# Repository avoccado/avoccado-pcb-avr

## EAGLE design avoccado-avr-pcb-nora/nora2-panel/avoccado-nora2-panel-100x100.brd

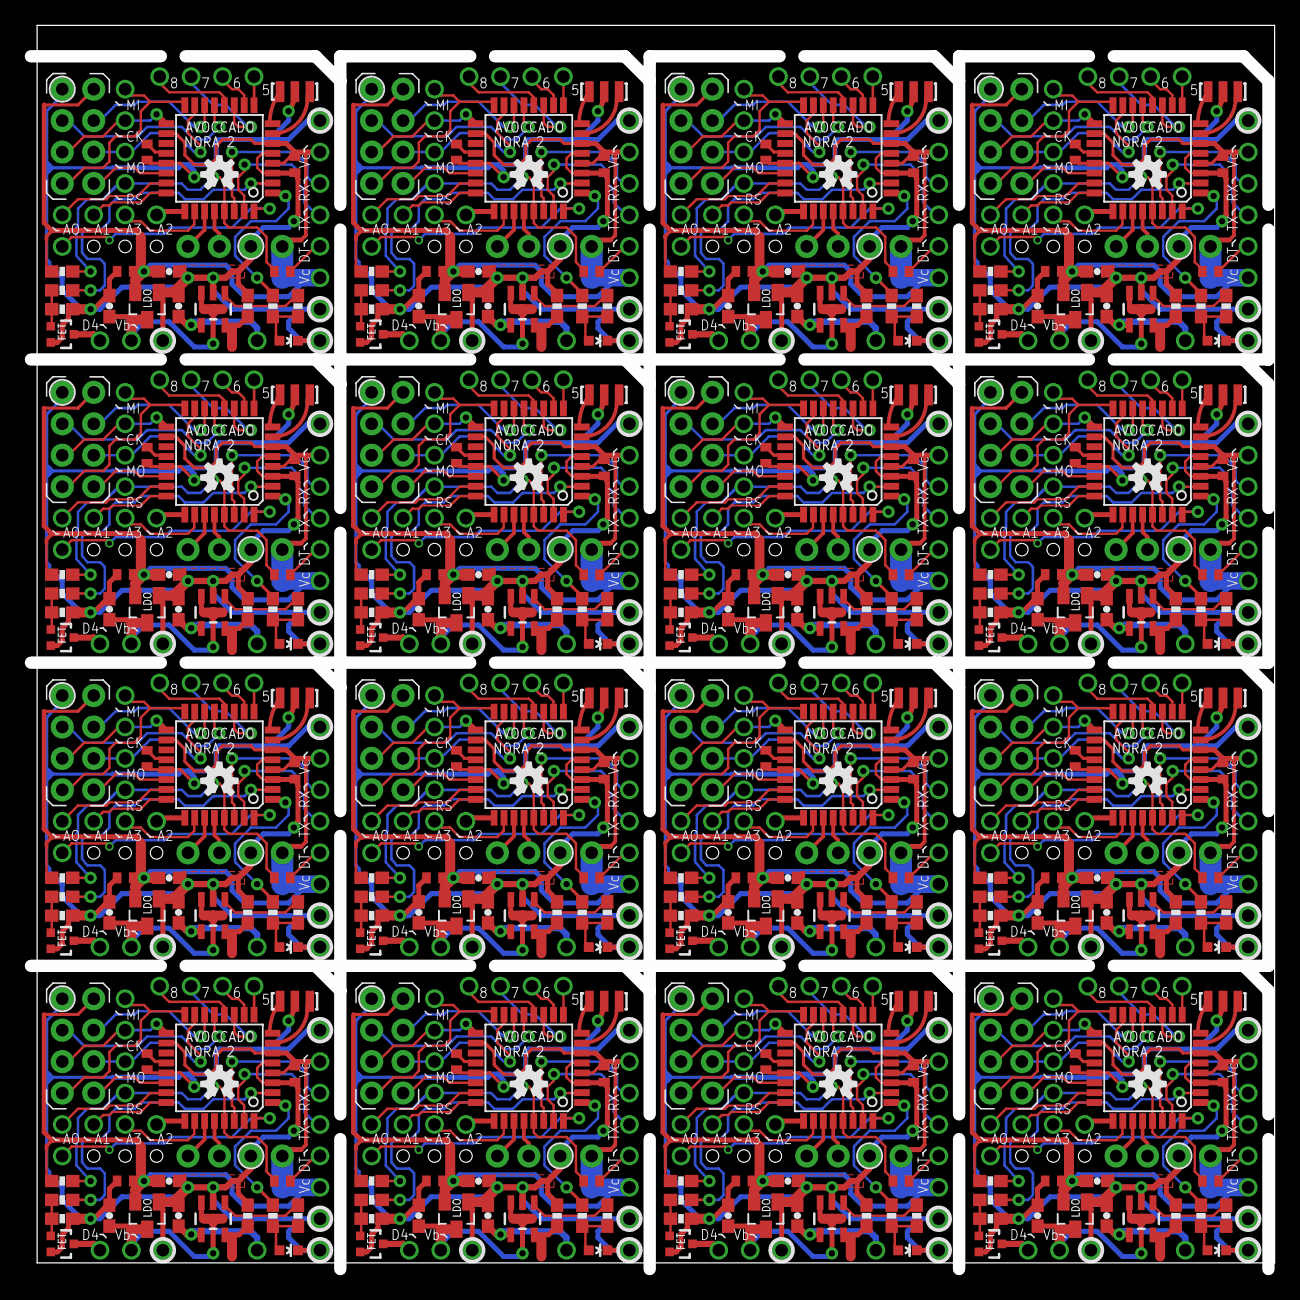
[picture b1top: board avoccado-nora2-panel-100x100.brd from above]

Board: 2 copper layers, 100.0 x 100.0 mm, 816 parts (0 on the bottom side), 560 nets.

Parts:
AVR, AVR1, AVR2, AVR3, AVR4, AVR5, AVR6, AVR7, AVR8, AVR9, AVR10, AVR11, AVR12, AVR13, AVR14, AVR15: ATMEGA328P; TQFP32-08
C1, C2, C3, C7, C8, C9, C10, C12, C15, C16, C17, C19, C22, C23, C24, C26, C29, C30, C31, C33, C36, C37, C38, C40, C43, C44, C45, C47, C50, C51, C52, C54, C57, C58, C59, C61, C64, C65, C66, C68, C71, C72, C73, C75, C78, C79, C80, C82, C85, C86, C87, C89, C92, C93, C94, C96, C99, C100, C101, C103, C106, C107, C108, C110: 0.1uF; C0402
C4, C5, C6, C11, C13, C14, C18, C20, C21, C25, C27, C28, C32, C34, C35, C39, C41, C42, C46, C48, C49, C53, C55, C56, C60, C62, C63, C67, C69, C70, C74, C76, C77, C81, C83, C84, C88, C90, C91, C95, C97, C98, C102, C104, C105, C109, C111, C112: 4.7uF; 0603-CAP
D1, D2, D3, D4, D5, D6, D7, D8, D9, D10, D11, D12, D13, D14, D15, D16: LED; LED-0603
JP1, JP3, JP6, JP7, JP8, JP9, JP10, JP11, JP12, JP13, JP14, JP15, JP16, JP17, JP18, JP19, JP20, JP21, JP22, JP23, JP24, JP25, JP26, JP30, JP31, JP32, JP33, JP34, JP35, JP36, JP37, JP38, JP39, JP40, JP41, JP42, JP43, JP44, JP45, JP46, JP53, JP54, JP55, JP56, JP57, JP58, JP59, JP60, JP61, JP62, JP63, JP64, JP65, JP66, JP67, JP68, JP69, JP70, JP71, JP72, JP79, JP80, JP81, JP82, JP83, JP84, JP85, JP86, JP87, JP88, JP89, JP90, JP91, JP92, JP93, JP94, JP95, JP96, JP97, JP98, JP105, JP106, JP107, JP108, JP109, JP110, JP111, JP112, JP113, JP114, JP115, JP116, JP117, JP118, JP119, JP120, JP121, JP122, JP123, JP124, JP131, JP132, JP133, JP134, JP135, JP136, JP137, JP138, JP139, JP140, JP141, JP142, JP143, JP144, JP145, JP146, JP147, JP148, JP149, JP150, JP157, JP158, JP159, JP160, JP161, JP162, JP163, JP164, JP165, JP166, JP167, JP168, JP169, JP170, JP171, JP172, JP173, JP174, JP175, JP176, JP183, JP184, JP185, JP186, JP187, JP188, JP189, JP190, JP191, JP192, JP193, JP194, JP195, JP196, JP197, JP198, JP199, JP200, JP201, JP202, JP209, JP210, JP211, JP212, JP213, JP214, JP215, JP216, JP217, JP218, JP219, JP220, JP221, JP222, JP223, JP224, JP225, JP226, JP227, JP228, JP235, JP236, JP237, JP238, JP239, JP240, JP241, JP242, JP243, JP244, JP245, JP246, JP247, JP248, JP249, JP250, JP251, JP252, JP253, JP254, JP261, JP262, JP263, JP264, JP265, JP266, JP267, JP268, JP269, JP270, JP271, JP272, JP273, JP274, JP275, JP276, JP277, JP278, JP279, JP280, JP287, JP288, JP289, JP290, JP291, JP292, JP293, JP294, JP295, JP296, JP297, JP298, JP299, JP300, JP301, JP302, JP303, JP304, JP305, JP306, JP313, JP314, JP315, JP316, JP317, JP318, JP319, JP320, JP321, JP322, JP323, JP324, JP325, JP326, JP327, JP328, JP329, JP330, JP331, JP332, JP339, JP340, JP341, JP342, JP343, JP344, JP345, JP346, JP347, JP348, JP349, JP350, JP351, JP352, JP353, JP354, JP355, JP356, JP357, JP358, JP365, JP366, JP367, JP368, JP369, JP370, JP371, JP372, JP373, JP374, JP375, JP376, JP377, JP378, JP379, JP380, JP381, JP382, JP383, JP384, JP391, JP392, JP393, JP394, JP395, JP396, JP397, JP398, JP399, JP400, JP401, JP402, JP403, JP404, JP405, JP406, JP407, JP408, JP409, JP410: M01NOSILK-KIT; 1X01NS-KIT
JP2, JP4, JP5, JP27, JP28, JP29, JP47, JP48, JP49, JP50, JP51, JP52, JP73, JP74, JP75, JP76, JP77, JP78, JP99, JP100, JP101, JP102, JP103, JP104, JP125, JP126, JP127, JP128, JP129, JP130, JP151, JP152, JP153, JP154, JP155, JP156, JP177, JP178, JP179, JP180, JP181, JP182, JP203, JP204, JP205, JP206, JP207, JP208, JP229, JP230, JP231, JP232, JP233, JP234, JP255, JP256, JP257, JP258, JP259, JP260, JP281, JP282, JP283, JP284, JP285, JP286, JP307, JP308, JP309, JP310, JP311, JP312, JP333, JP334, JP335, JP336, JP337, JP338, JP359, JP360, JP361, JP362, JP363, JP364, JP385, JP386, JP387, JP388, JP389, JP390, JP411, JP412, JP413, JP414, JP415, JP416: M021X02_NO_SILK; 1X02_NO_SILK
LDO, LDO1, LDO2, LDO3, LDO4, LDO5, LDO6, LDO7, LDO8, LDO9, LDO10, LDO11, LDO12, LDO13, LDO14, LDO15: MCP1703CB; SOT23
LOGO1, LOGO2, LOGO3, LOGO4, LOGO5, LOGO6, LOGO7, LOGO8, LOGO9, LOGO10, LOGO11, LOGO12, LOGO13, LOGO14, LOGO15, LOGO16: OSHW-LOGOS; OSHW-LOGO-S
Q1, Q3, Q5, Q7, Q9, Q11, Q13, Q15, Q17, Q19, Q21, Q23, Q25, Q27, Q29, Q31: 16MHz; RESONATOR-SMD
Q2, Q4, Q6, Q8, Q10, Q12, Q14, Q16, Q18, Q20, Q22, Q24, Q26, Q28, Q30, Q32: FET; SOT323
R1, R4, R6, R8, R10, R12, R14, R16, R18, R20, R22, R24, R26, R28, R30, R32, R34, R36, R38, R40, R42, R44, R46, R48, R50, R52, R54, R56, R58, R60, R62, R64, R66, R68, R70, R72, R74, R76, R78, R80, R82, R84, R86, R88, R90, R92, R94, R96: 1K; 0603-RES
R2, R7, R13, R19, R25, R31, R37, R43, R49, R55, R61, R67, R73, R79, R85, R91: 10K; 0603-RES
R3, R9, R15, R21, R27, R33, R39, R45, R51, R57, R63, R69, R75, R81, R87, R93: Rp; 0603-RES
R5, R11, R17, R23, R29, R35, R41, R47, R53, R59, R65, R71, R77, R83, R89, R95: 1M; 0603-RES
TP1, TP2, TP3, TP4, TP5, TP6, TP7, TP8, TP9, TP10, TP11, TP12, TP13, TP14, TP15, TP16, TP17, TP18, TP19, TP20, TP21, TP22, TP23, TP24, TP25, TP26, TP27, TP28, TP29, TP30, TP31, TP32, TP33, TP34, TP35, TP36, TP37, TP38, TP39, TP40, TP41, TP42, TP43, TP44, TP45, TP46, TP47, TP48, TP49, TP50, TP51, TP52, TP53, TP54, TP55, TP56, TP57, TP58, TP59, TP60, TP61, TP62, TP63, TP64, TP65, TP66, TP67, TP68, TP69, TP70, TP71, TP72, TP73, TP74, TP75, TP76, TP77, TP78, TP79, TP80: M01NOSILK-KIT; 1X01NS-KIT
U1, U2, U3, U4, U5, U6, U7, U8, U9, U10, U11, U12, U13, U14, U15, U16: MCP73831; SOT23-5

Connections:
3.3V: AVR.4, AVR.6, AVR.18, C3.2, C6.1, C10.1, JP2.2, JP4.1, JP11.1, JP18.1, LDO.2, R2.2
3.3V1: AVR1.4, AVR1.6, AVR1.18, C7.1, C8.2, C14.1, JP31.1, JP38.1, JP47.2, JP51.1, LDO1.2, R7.2
3.3V2: AVR2.4, AVR2.6, AVR2.18, C15.1, C16.2, C21.1, JP57.1, JP64.1, JP73.2, JP77.1, LDO2.2, R13.2
3.3V3: AVR3.4, AVR3.6, AVR3.18, C22.1, C23.2, C28.1, JP83.1, JP90.1, JP99.2, JP103.1, LDO3.2, R19.2
3.3V4: AVR4.4, AVR4.6, AVR4.18, C29.1, C30.2, C35.1, JP109.1, JP116.1, JP125.2, JP129.1, LDO4.2, R25.2
3.3V5: AVR5.4, AVR5.6, AVR5.18, C36.1, C37.2, C42.1, JP135.1, JP142.1, JP151.2, JP155.1, LDO5.2, R31.2
3.3V6: AVR6.4, AVR6.6, AVR6.18, C43.1, C44.2, C49.1, JP161.1, JP168.1, JP177.2, JP181.1, LDO6.2, R37.2
3.3V7: AVR7.4, AVR7.6, AVR7.18, C50.1, C51.2, C56.1, JP187.1, JP194.1, JP203.2, JP207.1, LDO7.2, R43.2
3.3V8: AVR8.4, AVR8.6, AVR8.18, C57.1, C58.2, C63.1, JP213.1, JP220.1, JP229.2, JP233.1, LDO8.2, R49.2
3.3V9: AVR9.4, AVR9.6, AVR9.18, C64.1, C65.2, C70.1, JP239.1, JP246.1, JP255.2, JP259.1, LDO9.2, R55.2
3.3V10: AVR10.4, AVR10.6, AVR10.18, C71.1, C72.2, C77.1, JP265.1, JP272.1, JP281.2, JP285.1, LDO10.2, R61.2
3.3V11: AVR11.4, AVR11.6, AVR11.18, C78.1, C79.2, C84.1, JP291.1, JP298.1, JP307.2, JP311.1, LDO11.2, R67.2
3.3V12: AVR12.4, AVR12.6, AVR12.18, C85.1, C86.2, C91.1, JP317.1, JP324.1, JP333.2, JP337.1, LDO12.2, R73.2
3.3V13: AVR13.4, AVR13.6, AVR13.18, C92.1, C93.2, C98.1, JP343.1, JP350.1, JP359.2, JP363.1, LDO13.2, R79.2
3.3V14: AVR14.4, AVR14.6, AVR14.18, C99.1, C100.2, C105.1, JP369.1, JP376.1, JP385.2, JP389.1, LDO14.2, R85.2
3.3V15: AVR15.4, AVR15.6, AVR15.18, C106.1, C107.2, C112.1, JP395.1, JP402.1, JP411.2, JP415.1, LDO15.2, R91.2
5V: C4.1, JP17.1, U2.4
5V1: C11.1, JP37.1, U1.4
5V2: C18.1, JP63.1, U3.4
5V3: C25.1, JP89.1, U4.4
5V4: C32.1, JP115.1, U5.4
5V5: C39.1, JP141.1, U6.4
5V6: C46.1, JP167.1, U7.4
5V7: C53.1, JP193.1, U8.4
5V8: C60.1, JP219.1, U9.4
5V9: C67.1, JP245.1, U10.4
5V10: C74.1, JP271.1, U11.4
5V11: C81.1, JP297.1, U12.4
5V12: C88.1, JP323.1, U13.4
5V13: C95.1, JP349.1, U14.4
5V14: C102.1, JP375.1, U15.4
5V15: C109.1, JP401.1, U16.4
A0: AVR.23, JP19.1
A1: AVR.24, JP20.1
A2: AVR.25, JP21.1
A3: AVR.26, JP22.1
A4: AVR.27, JP5.2
A5: AVR.28, JP5.1
A7: AVR1.28, JP52.1
A7-NRF-IRQ: AVR.22, JP29.2
A7-NRF-IRQ1: AVR1.22, JP50.2
A7-NRF-IRQ2: AVR2.22, JP76.2
A7-NRF-IRQ3: AVR3.22, JP102.2
A7-NRF-IRQ4: AVR4.22, JP128.2
A7-NRF-IRQ5: AVR5.22, JP154.2
A7-NRF-IRQ6: AVR6.22, JP180.2
A7-NRF-IRQ7: AVR7.22, JP206.2
A7-NRF-IRQ8: AVR8.22, JP232.2
A7-NRF-IRQ9: AVR9.22, JP258.2
A7-NRF-IRQ10: AVR10.22, JP284.2
A7-NRF-IRQ11: AVR11.22, JP310.2
A7-NRF-IRQ12: AVR12.22, JP336.2
A7-NRF-IRQ13: AVR13.22, JP362.2
A7-NRF-IRQ14: AVR14.22, JP388.2
A7-NRF-IRQ15: AVR15.22, JP414.2
A8: AVR1.27, JP52.2
A9: AVR1.26, JP42.1
A10: AVR1.25, JP41.1
A11: AVR1.24, JP40.1
A12: AVR1.23, JP39.1
A14: AVR2.28, JP78.1
A15: AVR2.27, JP78.2
A16: AVR2.26, JP68.1
A17: AVR2.25, JP67.1
A18: AVR2.24, JP66.1
A19: AVR2.23, JP65.1
A21: AVR3.28, JP104.1
A22: AVR3.27, JP104.2
A23: AVR3.26, JP94.1
A24: AVR3.25, JP93.1
A25: AVR3.24, JP92.1
A26: AVR3.23, JP91.1
A28: AVR4.28, JP130.1
A29: AVR4.27, JP130.2
A30: AVR4.26, JP120.1
A31: AVR4.25, JP119.1
A32: AVR4.24, JP118.1
A33: AVR4.23, JP117.1
A35: AVR5.28, JP156.1
A36: AVR5.27, JP156.2
A37: AVR5.26, JP146.1
A38: AVR5.25, JP145.1
A39: AVR5.24, JP144.1
A40: AVR5.23, JP143.1
A42: AVR6.28, JP182.1
A43: AVR6.27, JP182.2
A44: AVR6.26, JP172.1
A45: AVR6.25, JP171.1
A46: AVR6.24, JP170.1
A47: AVR6.23, JP169.1
A49: AVR7.28, JP208.1
A50: AVR7.27, JP208.2
A51: AVR7.26, JP198.1
A52: AVR7.25, JP197.1
A53: AVR7.24, JP196.1
A54: AVR7.23, JP195.1
A56: AVR8.28, JP234.1
A57: AVR8.27, JP234.2
A58: AVR8.26, JP224.1
A59: AVR8.25, JP223.1
A60: AVR8.24, JP222.1
A61: AVR8.23, JP221.1
A63: AVR9.28, JP260.1
A64: AVR9.27, JP260.2
A65: AVR9.26, JP250.1
A66: AVR9.25, JP249.1
A67: AVR9.24, JP248.1
A68: AVR9.23, JP247.1
A70: AVR10.28, JP286.1
A71: AVR10.27, JP286.2
A72: AVR10.26, JP276.1
A73: AVR10.25, JP275.1
A74: AVR10.24, JP274.1
A75: AVR10.23, JP273.1
A77: AVR11.28, JP312.1
A78: AVR11.27, JP312.2
A79: AVR11.26, JP302.1
A80: AVR11.25, JP301.1
A81: AVR11.24, JP300.1
A82: AVR11.23, JP299.1
A84: AVR12.28, JP338.1
A85: AVR12.27, JP338.2
A86: AVR12.26, JP328.1
A87: AVR12.25, JP327.1
A88: AVR12.24, JP326.1
A89: AVR12.23, JP325.1
A91: AVR13.28, JP364.1
A92: AVR13.27, JP364.2
A93: AVR13.26, JP354.1
A94: AVR13.25, JP353.1
A95: AVR13.24, JP352.1
A96: AVR13.23, JP351.1
A98: AVR14.28, JP390.1
A99: AVR14.27, JP390.2
A100: AVR14.26, JP380.1
A101: AVR14.25, JP379.1
A102: AVR14.24, JP378.1
A103: AVR14.23, JP377.1
A105: AVR15.28, JP416.1
A106: AVR15.27, JP416.2
A107: AVR15.26, JP406.1
A108: AVR15.25, JP405.1
A109: AVR15.24, JP404.1
A110: AVR15.23, JP403.1
AREF: AVR.20, C1.2
AREF1: AVR1.20, C9.2
AREF2: AVR2.20, C17.2
AREF3: AVR3.20, C24.2
AREF4: AVR4.20, C31.2
AREF5: AVR5.20, C38.2
AREF6: AVR6.20, C45.2
AREF7: AVR7.20, C52.2
AREF8: AVR8.20, C59.2
AREF9: AVR9.20, C66.2
AREF10: AVR10.20, C73.2
AREF11: AVR11.20, C80.2
AREF12: AVR12.20, C87.2
AREF13: AVR13.20, C94.2
AREF14: AVR14.20, C101.2
AREF15: AVR15.20, C108.2
CHG-PROG: R3.2, U2.5
CHG-PROG1: R9.2, U1.5
CHG-PROG2: R15.2, U3.5
CHG-PROG3: R21.2, U4.5
CHG-PROG4: R27.2, U5.5
CHG-PROG5: R33.2, U6.5
CHG-PROG6: R39.2, U7.5
CHG-PROG7: R45.2, U8.5
CHG-PROG8: R51.2, U9.5
CHG-PROG9: R57.2, U10.5
CHG-PROG10: R63.2, U11.5
CHG-PROG11: R69.2, U12.5
CHG-PROG12: R75.2, U13.5
CHG-PROG13: R81.2, U14.5
CHG-PROG14: R87.2, U15.5
CHG-PROG15: R93.2, U16.5
D1: AVR1.13, JP48.1
D2: AVR.32, TP2.1
D3: AVR.1, R6.1
D4: AVR.2, R1.1
D5: AVR.9, TP1.1
D6: AVR.10, TP6.1
D7: AVR.11, TP7.1
D8: AVR.12, TP8.1
D9: AVR.13, JP27.1
D10: AVR.14, JP27.2
D11: AVR1.12, TP9.1
D12: AVR1.32, TP10.1
D13: AVR1.1, R12.1
D14: AVR1.2, R8.1
D15: AVR1.9, TP3.1
D16: AVR1.10, TP4.1
D17: AVR1.11, TP5.1
D18: AVR1.14, JP48.2
D19: AVR2.13, JP74.1
D20: AVR2.12, TP14.1
D21: AVR2.32, TP15.1
D22: AVR2.1, R18.1
D23: AVR2.2, R14.1
D24: AVR2.9, TP11.1
D25: AVR2.10, TP12.1
D26: AVR2.11, TP13.1
D27: AVR2.14, JP74.2
D28: AVR3.13, JP100.1
D29: AVR3.12, TP19.1
D30: AVR3.32, TP20.1
D31: AVR3.1, R24.1
D32: AVR3.2, R20.1
D33: AVR3.9, TP16.1
D34: AVR3.10, TP17.1
D35: AVR3.11, TP18.1
D36: AVR3.14, JP100.2
D37: AVR4.13, JP126.1
D38: AVR4.12, TP24.1
D39: AVR4.32, TP25.1
D40: AVR4.1, R30.1
D41: AVR4.2, R26.1
D42: AVR4.9, TP21.1
D43: AVR4.10, TP22.1
D44: AVR4.11, TP23.1
D45: AVR4.14, JP126.2
D46: AVR5.13, JP152.1
D47: AVR5.12, TP29.1
D48: AVR5.32, TP30.1
D49: AVR5.1, R36.1
D50: AVR5.2, R32.1
D51: AVR5.9, TP26.1
D52: AVR5.10, TP27.1
D53: AVR5.11, TP28.1
D54: AVR5.14, JP152.2
D55: AVR6.13, JP178.1
D56: AVR6.12, TP34.1
D57: AVR6.32, TP35.1
D58: AVR6.1, R42.1
D59: AVR6.2, R38.1
D60: AVR6.9, TP31.1
D61: AVR6.10, TP32.1
D62: AVR6.11, TP33.1
D63: AVR6.14, JP178.2
D64: AVR7.13, JP204.1
D65: AVR7.12, TP39.1
D66: AVR7.32, TP40.1
D67: AVR7.1, R48.1
D68: AVR7.2, R44.1
D69: AVR7.9, TP36.1
D70: AVR7.10, TP37.1
D71: AVR7.11, TP38.1
D72: AVR7.14, JP204.2
D73: AVR8.13, JP230.1
D74: AVR8.12, TP44.1
D75: AVR8.32, TP45.1
D76: AVR8.1, R54.1
D77: AVR8.2, R50.1
D78: AVR8.9, TP41.1
D79: AVR8.10, TP42.1
D80: AVR8.11, TP43.1
D81: AVR8.14, JP230.2
D82: AVR9.13, JP256.1
D83: AVR9.12, TP49.1
D84: AVR9.32, TP50.1
D85: AVR9.1, R60.1
D86: AVR9.2, R56.1
D87: AVR9.9, TP46.1
D88: AVR9.10, TP47.1
D89: AVR9.11, TP48.1
D90: AVR9.14, JP256.2
D91: AVR10.13, JP282.1
D92: AVR10.12, TP54.1
D93: AVR10.32, TP55.1
D94: AVR10.1, R66.1
D95: AVR10.2, R62.1
D96: AVR10.9, TP51.1
D97: AVR10.10, TP52.1
D98: AVR10.11, TP53.1
D99: AVR10.14, JP282.2
D100: AVR11.13, JP308.1
D101: AVR11.12, TP59.1
D102: AVR11.32, TP60.1
D103: AVR11.1, R72.1
D104: AVR11.2, R68.1
D105: AVR11.9, TP56.1
D106: AVR11.10, TP57.1
D107: AVR11.11, TP58.1
D108: AVR11.14, JP308.2
D109: AVR12.13, JP334.1
D110: AVR12.12, TP64.1
D111: AVR12.32, TP65.1
D112: AVR12.1, R78.1
D113: AVR12.2, R74.1
D114: AVR12.9, TP61.1
D115: AVR12.10, TP62.1
D116: AVR12.11, TP63.1
D117: AVR12.14, JP334.2
D118: AVR13.13, JP360.1
D119: AVR13.12, TP69.1
D120: AVR13.32, TP70.1
D121: AVR13.1, R84.1
D122: AVR13.2, R80.1
D123: AVR13.9, TP66.1
D124: AVR13.10, TP67.1
D125: AVR13.11, TP68.1
D126: AVR13.14, JP360.2
D127: AVR14.13, JP386.1
D128: AVR14.12, TP74.1
D129: AVR14.32, TP75.1
D130: AVR14.1, R90.1
D131: AVR14.2, R86.1
D132: AVR14.9, TP71.1
D133: AVR14.10, TP72.1
D134: AVR14.11, TP73.1
D135: AVR14.14, JP386.2
D136: AVR15.13, JP412.1
D137: AVR15.12, TP79.1
D138: AVR15.32, TP80.1
D139: AVR15.1, R96.1
D140: AVR15.2, R92.1
D141: AVR15.9, TP76.1
D142: AVR15.10, TP77.1
D143: AVR15.11, TP78.1
D144: AVR15.14, JP412.2
DTR: C2.2, JP10.1
DTR1: C12.2, JP30.1
DTR2: C19.2, JP56.1
DTR3: C26.2, JP82.1
DTR4: C33.2, JP108.1
DTR5: C40.2, JP134.1
DTR6: C47.2, JP160.1
DTR7: C54.2, JP186.1
DTR8: C61.2, JP212.1
DTR9: C68.2, JP238.1
DTR10: C75.2, JP264.1
DTR11: C82.2, JP290.1
DTR12: C89.2, JP316.1
DTR13: C96.2, JP342.1
DTR14: C103.2, JP368.1
DTR15: C110.2, JP394.1
GND: AVR.3, AVR.5, AVR.21, C1.1, C3.1, C4.2, C5.2, C6.2, C10.2, D1.C, JP2.1, JP3.1, JP4.2, JP6.1, JP25.1, JP26.1, LDO.1, Q1.2, Q2.2, R3.1, R5.1, U2.2
GND1: AVR1.3, AVR1.5, AVR1.21, C7.2, C8.1, C9.1, C11.2, C13.2, C14.2, D2.C, JP1.1, JP36.1, JP45.1, JP46.1, JP47.1, JP51.2, LDO1.1, Q3.2, Q4.2, R9.1, R11.1, U1.2
GND2: AVR2.3, AVR2.5, AVR2.21, C15.2, C16.1, C17.1, C18.2, C20.2, C21.2, D3.C, JP53.1, JP62.1, JP71.1, JP72.1, JP73.1, JP77.2, LDO2.1, Q5.2, Q6.2, R15.1, R17.1, U3.2
GND3: AVR3.3, AVR3.5, AVR3.21, C22.2, C23.1, C24.1, C25.2, C27.2, C28.2, D4.C, JP79.1, JP88.1, JP97.1, JP98.1, JP99.1, JP103.2, LDO3.1, Q7.2, Q8.2, R21.1, R23.1, U4.2
GND4: AVR4.3, AVR4.5, AVR4.21, C29.2, C30.1, C31.1, C32.2, C34.2, C35.2, D5.C, JP105.1, JP114.1, JP123.1, JP124.1, JP125.1, JP129.2, LDO4.1, Q9.2, Q10.2, R27.1, R29.1, U5.2
GND5: AVR5.3, AVR5.5, AVR5.21, C36.2, C37.1, C38.1, C39.2, C41.2, C42.2, D6.C, JP131.1, JP140.1, JP149.1, JP150.1, JP151.1, JP155.2, LDO5.1, Q11.2, Q12.2, R33.1, R35.1, U6.2
GND6: AVR6.3, AVR6.5, AVR6.21, C43.2, C44.1, C45.1, C46.2, C48.2, C49.2, D7.C, JP157.1, JP166.1, JP175.1, JP176.1, JP177.1, JP181.2, LDO6.1, Q13.2, Q14.2, R39.1, R41.1, U7.2
GND7: AVR7.3, AVR7.5, AVR7.21, C50.2, C51.1, C52.1, C53.2, C55.2, C56.2, D8.C, JP183.1, JP192.1, JP201.1, JP202.1, JP203.1, JP207.2, LDO7.1, Q15.2, Q16.2, R45.1, R47.1, U8.2
GND8: AVR8.3, AVR8.5, AVR8.21, C57.2, C58.1, C59.1, C60.2, C62.2, C63.2, D9.C, JP209.1, JP218.1, JP227.1, JP228.1, JP229.1, JP233.2, LDO8.1, Q17.2, Q18.2, R51.1, R53.1, U9.2
GND9: AVR9.3, AVR9.5, AVR9.21, C64.2, C65.1, C66.1, C67.2, C69.2, C70.2, D10.C, JP235.1, JP244.1, JP253.1, JP254.1, JP255.1, JP259.2, LDO9.1, Q19.2, Q20.2, R57.1, R59.1, U10.2
GND10: AVR10.3, AVR10.5, AVR10.21, C71.2, C72.1, C73.1, C74.2, C76.2, C77.2, D11.C, JP261.1, JP270.1, JP279.1, JP280.1, JP281.1, JP285.2, LDO10.1, Q21.2, Q22.2, R63.1, R65.1, U11.2
GND11: AVR11.3, AVR11.5, AVR11.21, C78.2, C79.1, C80.1, C81.2, C83.2, C84.2, D12.C, JP287.1, JP296.1, JP305.1, JP306.1, JP307.1, JP311.2, LDO11.1, Q23.2, Q24.2, R69.1, R71.1, U12.2
GND12: AVR12.3, AVR12.5, AVR12.21, C85.2, C86.1, C87.1, C88.2, C90.2, C91.2, D13.C, JP313.1, JP322.1, JP331.1, JP332.1, JP333.1, JP337.2, LDO12.1, Q25.2, Q26.2, R75.1, R77.1, U13.2
GND13: AVR13.3, AVR13.5, AVR13.21, C92.2, C93.1, C94.1, C95.2, C97.2, C98.2, D14.C, JP339.1, JP348.1, JP357.1, JP358.1, JP359.1, JP363.2, LDO13.1, Q27.2, Q28.2, R81.1, R83.1, U14.2
GND14: AVR14.3, AVR14.5, AVR14.21, C99.2, C100.1, C101.1, C102.2, C104.2, C105.2, D15.C, JP365.1, JP374.1, JP383.1, JP384.1, JP385.1, JP389.2, LDO14.1, Q29.2, Q30.2, R87.1, R89.1, U15.2
GND15: AVR15.3, AVR15.5, AVR15.21, C106.2, C107.1, C108.1, C109.2, C111.2, C112.2, D16.C, JP391.1, JP400.1, JP409.1, JP410.1, JP411.1, JP415.2, LDO15.1, Q31.2, Q32.2, R93.1, R95.1, U16.2
LED: D1.A, R4.1, R6.2
LED1: D2.A, R10.1, R12.2
LED2: D3.A, R16.1, R18.2
LED3: D4.A, R22.1, R24.2
LED4: D5.A, R28.1, R30.2
LED5: D6.A, R34.1, R36.2
LED6: D7.A, R40.1, R42.2
LED7: D8.A, R46.1, R48.2
LED8: D9.A, R52.1, R54.2
LED9: D10.A, R58.1, R60.2
LED10: D11.A, R64.1, R66.2
LED11: D12.A, R70.1, R72.2
LED12: D13.A, R76.1, R78.2
LED13: D14.A, R82.1, R84.2
LED14: D15.A, R88.1, R90.2
LED15: D16.A, R94.1, R96.2
MISO: AVR.16, JP12.1, JP29.1
MISO1: AVR1.16, JP32.1, JP50.1
MISO2: AVR2.16, JP58.1, JP76.1
MISO3: AVR3.16, JP84.1, JP102.1
MISO4: AVR4.16, JP110.1, JP128.1
MISO5: AVR5.16, JP136.1, JP154.1
MISO6: AVR6.16, JP162.1, JP180.1
MISO7: AVR7.16, JP188.1, JP206.1
MISO8: AVR8.16, JP214.1, JP232.1
MISO9: AVR9.16, JP240.1, JP258.1
MISO10: AVR10.16, JP266.1, JP284.1
MISO11: AVR11.16, JP292.1, JP310.1
MISO12: AVR12.16, JP318.1, JP336.1
MISO13: AVR13.16, JP344.1, JP362.1
MISO14: AVR14.16, JP370.1, JP388.1
MISO15: AVR15.16, JP396.1, JP414.1
MOSI: AVR.15, JP14.1, JP28.2
MOSI1: AVR1.15, JP34.1, JP49.2
MOSI2: AVR2.15, JP60.1, JP75.2
MOSI3: AVR3.15, JP86.1, JP101.2
MOSI4: AVR4.15, JP112.1, JP127.2
MOSI5: AVR5.15, JP138.1, JP153.2
MOSI6: AVR6.15, JP164.1, JP179.2
MOSI7: AVR7.15, JP190.1, JP205.2
MOSI8: AVR8.15, JP216.1, JP231.2
MOSI9: AVR9.15, JP242.1, JP257.2
MOSI10: AVR10.15, JP268.1, JP283.2
MOSI11: AVR11.15, JP294.1, JP309.2
MOSI12: AVR12.15, JP320.1, JP335.2
MOSI13: AVR13.15, JP346.1, JP361.2
MOSI14: AVR14.15, JP372.1, JP387.2
MOSI15: AVR15.15, JP398.1, JP413.2
unnamed: AVR.8, Q1.1
unnamed: AVR.7, Q1.3
unnamed: AVR1.8, Q3.1
unnamed: AVR1.7, Q3.3
unnamed: Q4.1, R8.2, R11.2
unnamed: Q2.1, R1.2, R5.2
unnamed: AVR2.8, Q5.1
unnamed: AVR2.7, Q5.3
unnamed: Q6.1, R14.2, R17.2
unnamed: AVR3.8, Q7.1
unnamed: AVR3.7, Q7.3
unnamed: Q8.1, R20.2, R23.2
unnamed: AVR4.8, Q9.1
unnamed: AVR4.7, Q9.3
unnamed: Q10.1, R26.2, R29.2
unnamed: AVR5.8, Q11.1
unnamed: AVR5.7, Q11.3
unnamed: Q12.1, R32.2, R35.2
unnamed: AVR6.8, Q13.1
unnamed: AVR6.7, Q13.3
unnamed: Q14.1, R38.2, R41.2
unnamed: AVR7.8, Q15.1
unnamed: AVR7.7, Q15.3
unnamed: Q16.1, R44.2, R47.2
unnamed: AVR8.8, Q17.1
unnamed: AVR8.7, Q17.3
unnamed: Q18.1, R50.2, R53.2
unnamed: AVR9.8, Q19.1
unnamed: AVR9.7, Q19.3
unnamed: Q20.1, R56.2, R59.2
unnamed: AVR10.8, Q21.1
unnamed: AVR10.7, Q21.3
unnamed: Q22.1, R62.2, R65.2
unnamed: AVR11.8, Q23.1
unnamed: AVR11.7, Q23.3
unnamed: Q24.1, R68.2, R71.2
unnamed: AVR12.8, Q25.1
unnamed: AVR12.7, Q25.3
unnamed: Q26.1, R74.2, R77.2
unnamed: AVR13.8, Q27.1
unnamed: AVR13.7, Q27.3
unnamed: Q28.1, R80.2, R83.2
unnamed: AVR14.8, Q29.1
unnamed: AVR14.7, Q29.3
unnamed: Q30.1, R86.2, R89.2
unnamed: AVR15.8, Q31.1
unnamed: AVR15.7, Q31.3
unnamed: Q32.1, R92.2, R95.2
RESET: AVR.29, C2.1, JP15.1, R2.1
RESET1: AVR1.29, C12.1, JP35.1, R7.1
RESET2: AVR2.29, C19.1, JP61.1, R13.1
RESET3: AVR3.29, C26.1, JP87.1, R19.1
RESET4: AVR4.29, C33.1, JP113.1, R25.1
RESET5: AVR5.29, C40.1, JP139.1, R31.1
RESET6: AVR6.29, C47.1, JP165.1, R37.1
RESET7: AVR7.29, C54.1, JP191.1, R43.1
RESET8: AVR8.29, C61.1, JP217.1, R49.1
RESET9: AVR9.29, C68.1, JP243.1, R55.1
RESET10: AVR10.29, C75.1, JP269.1, R61.1
RESET11: AVR11.29, C82.1, JP295.1, R67.1
RESET12: AVR12.29, C89.1, JP321.1, R73.1
RESET13: AVR13.29, C96.1, JP347.1, R79.1
RESET14: AVR14.29, C103.1, JP373.1, R85.1
RESET15: AVR15.29, C110.1, JP399.1, R91.1
RXI: AVR.30, JP8.1
RXI1: AVR1.30, JP7.1
RXI2: AVR2.30, JP54.1
RXI3: AVR3.30, JP80.1
RXI4: AVR4.30, JP106.1
RXI5: AVR5.30, JP132.1
RXI6: AVR6.30, JP158.1
RXI7: AVR7.30, JP184.1
RXI8: AVR8.30, JP210.1
RXI9: AVR9.30, JP236.1
RXI10: AVR10.30, JP262.1
RXI11: AVR11.30, JP288.1
RXI12: AVR12.30, JP314.1
RXI13: AVR13.30, JP340.1
RXI14: AVR14.30, JP366.1
RXI15: AVR15.30, JP392.1
SCK: AVR.17, JP13.1, JP28.1
SCK1: AVR1.17, JP33.1, JP49.1
SCK2: AVR2.17, JP59.1, JP75.1
SCK3: AVR3.17, JP85.1, JP101.1
SCK4: AVR4.17, JP111.1, JP127.1
SCK5: AVR5.17, JP137.1, JP153.1
SCK6: AVR6.17, JP163.1, JP179.1
SCK7: AVR7.17, JP189.1, JP205.1
SCK8: AVR8.17, JP215.1, JP231.1
SCK9: AVR9.17, JP241.1, JP257.1
SCK10: AVR10.17, JP267.1, JP283.1
SCK11: AVR11.17, JP293.1, JP309.1
SCK12: AVR12.17, JP319.1, JP335.1
SCK13: AVR13.17, JP345.1, JP361.1
SCK14: AVR14.17, JP371.1, JP387.1
SCK15: AVR15.17, JP397.1, JP413.1
SOC: R4.2, U2.1
SOC1: R10.2, U1.1
SOC2: R16.2, U3.1
SOC3: R22.2, U4.1
SOC4: R28.2, U5.1
SOC5: R34.2, U6.1
SOC6: R40.2, U7.1
SOC7: R46.2, U8.1
SOC8: R52.2, U9.1
SOC9: R58.2, U10.1
SOC10: R64.2, U11.1
SOC11: R70.2, U12.1
SOC12: R76.2, U13.1
SOC13: R82.2, U14.1
SOC14: R88.2, U15.1
SOC15: R94.2, U16.1
TXO: AVR.31, JP9.1
TXO1: AVR1.31, JP16.1
TXO2: AVR2.31, JP55.1
TXO3: AVR3.31, JP81.1
TXO4: AVR4.31, JP107.1
TXO5: AVR5.31, JP133.1
TXO6: AVR6.31, JP159.1
TXO7: AVR7.31, JP185.1
TXO8: AVR8.31, JP211.1
TXO9: AVR9.31, JP237.1
TXO10: AVR10.31, JP263.1
TXO11: AVR11.31, JP289.1
TXO12: AVR12.31, JP315.1
TXO13: AVR13.31, JP341.1
TXO14: AVR14.31, JP367.1
TXO15: AVR15.31, JP393.1
VBAT: C5.1, JP24.1, LDO.3, U2.3
VBAT1: C13.1, JP43.1, LDO1.3, U1.3
VBAT2: C20.1, JP69.1, LDO2.3, U3.3
VBAT3: C27.1, JP95.1, LDO3.3, U4.3
VBAT4: C34.1, JP121.1, LDO4.3, U5.3
VBAT5: C41.1, JP147.1, LDO5.3, U6.3
VBAT6: C48.1, JP173.1, LDO6.3, U7.3
VBAT7: C55.1, JP199.1, LDO7.3, U8.3
VBAT8: C62.1, JP225.1, LDO8.3, U9.3
VBAT9: C69.1, JP251.1, LDO9.3, U10.3
VBAT10: C76.1, JP277.1, LDO10.3, U11.3
VBAT11: C83.1, JP303.1, LDO11.3, U12.3
VBAT12: C90.1, JP329.1, LDO12.3, U13.3
VBAT13: C97.1, JP355.1, LDO13.3, U14.3
VBAT14: C104.1, JP381.1, LDO14.3, U15.3
VBAT15: C111.1, JP407.1, LDO15.3, U16.3
VIBR: JP23.1, Q2.3
VIBR1: JP44.1, Q4.3
VIBR2: JP70.1, Q6.3
VIBR3: JP96.1, Q8.3
VIBR4: JP122.1, Q10.3
VIBR5: JP148.1, Q12.3
VIBR6: JP174.1, Q14.3
VIBR7: JP200.1, Q16.3
VIBR8: JP226.1, Q18.3
VIBR9: JP252.1, Q20.3
VIBR10: JP278.1, Q22.3
VIBR11: JP304.1, Q24.3
VIBR12: JP330.1, Q26.3
VIBR13: JP356.1, Q28.3
VIBR14: JP382.1, Q30.3
VIBR15: JP408.1, Q32.3

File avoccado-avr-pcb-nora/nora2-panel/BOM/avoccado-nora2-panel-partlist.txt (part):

Partlist

Exported from avoccado-nora2-panel-100x100.brd

EAGLE Version 7.2.0 Copyright (c) 1988-2014 CadSoft

Assembly variant: 

Part     Value           Package       Library               Position (inch)       Orientation

AVR      ATMEGA328P      TQFP32-08     SparkFun-DigitalIC    (0.58 0.62031496)     R180
AVR1     ATMEGA328P      TQFP32-08     SparkFun-DigitalIC    (1.56425197 0.62031496) R180
AVR2     ATMEGA328P      TQFP32-08     SparkFun-DigitalIC    (0.58 1.58488189)     R180
AVR3     ATMEGA328P      TQFP32-08     SparkFun-DigitalIC    (1.56425197 1.58488189) R180
AVR4     ATMEGA328P      TQFP32-08     SparkFun-DigitalIC    (2.54850394 0.62031496) R180
AVR5     ATMEGA328P      TQFP32-08     SparkFun-DigitalIC    (3.53275591 0.62031496) R180
AVR6     ATMEGA328P      TQFP32-08     SparkFun-DigitalIC    (2.54850394 1.58488189) R180
AVR7     ATMEGA328P      TQFP32-08     SparkFun-DigitalIC    (3.53275591 1.58488189) R180
AVR8     ATMEGA328P      TQFP32-08     SparkFun-DigitalIC    (0.58 2.54944882)     R180
AVR9     ATMEGA328P      TQFP32-08     SparkFun-DigitalIC    (1.56425197 2.54944882) R180
AVR10    ATMEGA328P      TQFP32-08     SparkFun-DigitalIC    (0.58 3.51401575)     R180
AVR11    ATMEGA328P      TQFP32-08     SparkFun-DigitalIC    (1.56425197 3.51401575) R180
AVR12    ATMEGA328P      TQFP32-08     SparkFun-DigitalIC    (2.54850394 2.54944882) R180
AVR13    ATMEGA328P      TQFP32-08     SparkFun-DigitalIC    (3.53275591 2.54944882) R180
AVR14    ATMEGA328P      TQFP32-08     SparkFun-DigitalIC    (2.54850394 3.51401575) R180
AVR15    ATMEGA328P      TQFP32-08     SparkFun-DigitalIC    (3.53275591 3.51401575) R180
C1       0.1uF           C0402         SparkFun              (0.35 0.64031496)     R90
C2       0.1uF           C0402         SparkFun              (0.78 0.26031496)     R0
C3       0.1uF           C0402         SparkFun              (0.82 0.60031496)     R90
C4       4.7uF           0603-CAP      SparkFun-Capacitors   (0.45 0.15031496)     R90
C5       4.7uF           0603-CAP      SparkFun-Capacitors   (0.23 0.15031496)     R90
C6       4.7uF           0603-CAP      SparkFun-Capacitors   (0.42 0.26031496)     R0
C7       0.1uF           C0402         SparkFun              (1.26425197 0.26031496) R180
C8       0.1uF           C0402         SparkFun              (1.80425197 0.60031496) R90
C9       0.1uF           C0402         SparkFun              (1.33425197 0.64031496) R90
C10      0.1uF           C0402         SparkFun              (0.28 0.26031496)     R180
C11      4.7uF           0603-CAP      SparkFun-Capacitors   (1.43425197 0.15031496) R90
C12      0.1uF           C0402         SparkFun              (1.76425197 0.26031496) R0
C13      4.7uF           0603-CAP      SparkFun-Capacitors   (1.21425197 0.15031496) R90
C14      4.7uF           0603-CAP      SparkFun-Capacitors   (1.40425197 0.26031496) R0
C15      0.1uF           C0402         SparkFun              (0.28 1.22488189)     R180
C16      0.1uF           C0402         SparkFun              (0.82 1.56488189)     R90
C17      0.1uF           C0402         SparkFun              (0.35 1.60488189)     R90
C18      4.7uF           0603-CAP      SparkFun-Capacitors   (0.45 1.11488189)     R90
C19      0.1uF           C0402         SparkFun              (0.78 1.22488189)     R0
C20      4.7uF           0603-CAP      SparkFun-Capacitors   (0.23 1.11488189)     R90
C21      4.7uF           0603-CAP      SparkFun-Capacitors   (0.42 1.22488189)     R0
C22      0.1uF           C0402         SparkFun              (1.26425197 1.22488189) R180
C23      0.1uF           C0402         SparkFun              (1.80425197 1.56488189) R90
C24      0.1uF           C0402         SparkFun              (1.33425197 1.60488189) R90
C25      4.7uF           0603-CAP      SparkFun-Capacitors   (1.43425197 1.11488189) R90
C26      0.1uF           C0402         SparkFun              (1.76425197 1.22488189) R0
C27      4.7uF           0603-CAP      SparkFun-Capacitors   (1.21425197 1.11488189) R90
C28      4.7uF           0603-CAP      SparkFun-Capacitors   (1.40425197 1.22488189) R0
C29      0.1uF           C0402         SparkFun              (2.24850394 0.26031496) R180
C30      0.1uF           C0402         SparkFun              (2.78850394 0.60031496) R90
C31      0.1uF           C0402         SparkFun              (2.31850394 0.64031496) R90
C32      4.7uF           0603-CAP      SparkFun-Capacitors   (2.41850394 0.15031496) R90
C33      0.1uF           C0402         SparkFun              (2.74850394 0.26031496) R0
C34      4.7uF           0603-CAP      SparkFun-Capacitors   (2.19850394 0.15031496) R90
C35      4.7uF           0603-CAP      SparkFun-Capacitors   (2.38850394 0.26031496) R0
C36      0.1uF           C0402         SparkFun              (3.23275591 0.26031496) R180
C37      0.1uF           C0402         SparkFun              (3.77275591 0.60031496) R90
C38      0.1uF           C0402         SparkFun              (3.30275591 0.64031496) R90
C39      4.7uF           0603-CAP      SparkFun-Capacitors   (3.40275591 0.15031496) R90
C40      0.1uF           C0402         SparkFun              (3.73275591 0.26031496) R0
C41      4.7uF           0603-CAP      SparkFun-Capacitors   (3.18275591 0.15031496) R90
C42      4.7uF           0603-CAP      SparkFun-Capacitors   (3.37275591 0.26031496) R0
C43      0.1uF           C0402         SparkFun              (2.24850394 1.22488189) R180
C44      0.1uF           C0402         SparkFun              (2.78850394 1.56488189) R90
C45      0.1uF           C0402         SparkFun              (2.31850394 1.60488189) R90
C46      4.7uF           0603-CAP      SparkFun-Capacitors   (2.41850394 1.11488189) R90
C47      0.1uF           C0402         SparkFun              (2.74850394 1.22488189) R0
C48      4.7uF           0603-CAP      SparkFun-Capacitors   (2.19850394 1.11488189) R90
C49      4.7uF           0603-CAP      SparkFun-Capacitors   (2.38850394 1.22488189) R0
C50      0.1uF           C0402         SparkFun              (3.23275591 1.22488189) R180
C51      0.1uF           C0402         SparkFun              (3.77275591 1.56488189) R90
C52      0.1uF           C0402         SparkFun              (3.30275591 1.60488189) R90
C53      4.7uF           0603-CAP      SparkFun-Capacitors   (3.40275591 1.11488189) R90
C54      0.1uF           C0402         SparkFun              (3.73275591 1.22488189) R0
C55      4.7uF           0603-CAP      SparkFun-Capacitors   (3.18275591 1.11488189) R90
C56      4.7uF           0603-CAP      SparkFun-Capacitors   (3.37275591 1.22488189) R0
C57      0.1uF           C0402         SparkFun              (0.28 2.18944882)     R180
C58      0.1uF           C0402         SparkFun              (0.82 2.52944882)     R90
C59      0.1uF           C0402         SparkFun              (0.35 2.56944882)     R90
C60      4.7uF           0603-CAP      SparkFun-Capacitors   (0.45 2.07944882)     R90
C61      0.1uF           C0402         SparkFun              (0.78 2.18944882)     R0
C62      4.7uF           0603-CAP      SparkFun-Capacitors   (0.23 2.07944882)     R90
C63      4.7uF           0603-CAP      SparkFun-Capacitors   (0.42 2.18944882)     R0
C64      0.1uF           C0402         SparkFun              (1.26425197 2.18944882) R180
C65      0.1uF           C0402         SparkFun              (1.80425197 2.52944882) R90
C66      0.1uF           C0402         SparkFun              (1.33425197 2.56944882) R90
C67      4.7uF           0603-CAP      SparkFun-Capacitors   (1.43425197 2.07944882) R90
C68      0.1uF           C0402         SparkFun              (1.76425197 2.18944882) R0
C69      4.7uF           0603-CAP      SparkFun-Capacitors   (1.21425197 2.07944882) R90
C70      4.7uF           0603-CAP      SparkFun-Capacitors   (1.40425197 2.18944882) R0
C71      0.1uF           C0402         SparkFun              (0.28 3.15401575)     R180
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

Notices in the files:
parts and their libraries:
SparkFun-DiscreteSemi: Licensing: Creative Commons ShareAlike 4.0 International - https://creativecommons.org/licenses/by-sa/4.0
